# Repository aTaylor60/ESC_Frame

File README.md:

# ESC_Frame
A combined frame and 4in1 brushless ESC running BLHeli_s with 16mm hole spacing.

Derived from the excelent [tinyPEPPER](http://fishpepper.de/projects/tinypepper/) project by http://fishpepper.de As such I have also used the fishpepper KiCad resources - [kicad_misc](https://github.com/fishpepper/kicad_misc) 

Until I write a proper build guide the [tinyPEPPER v0.5](http://fishpepper.de/2017/03/23/tinypepper-esc-how-to-build-your-own-v0-5/) build guide will be the best reference.

Key features:
- Frame integrated ESC reduces stack height
- 83mm motor-to-motor frame size suits BR1103b motors
- 16x16mm hole-to-hole spacing for FC
- BLHeli_S with DSHOT300
- 1S only

This work is published under the CERN open hardware license v1.2. 
Feel free to use the design - but make sure to give proper credit 
and release all modifications under the same license! 

This comes with NO warranty, build and fly at your own risk!

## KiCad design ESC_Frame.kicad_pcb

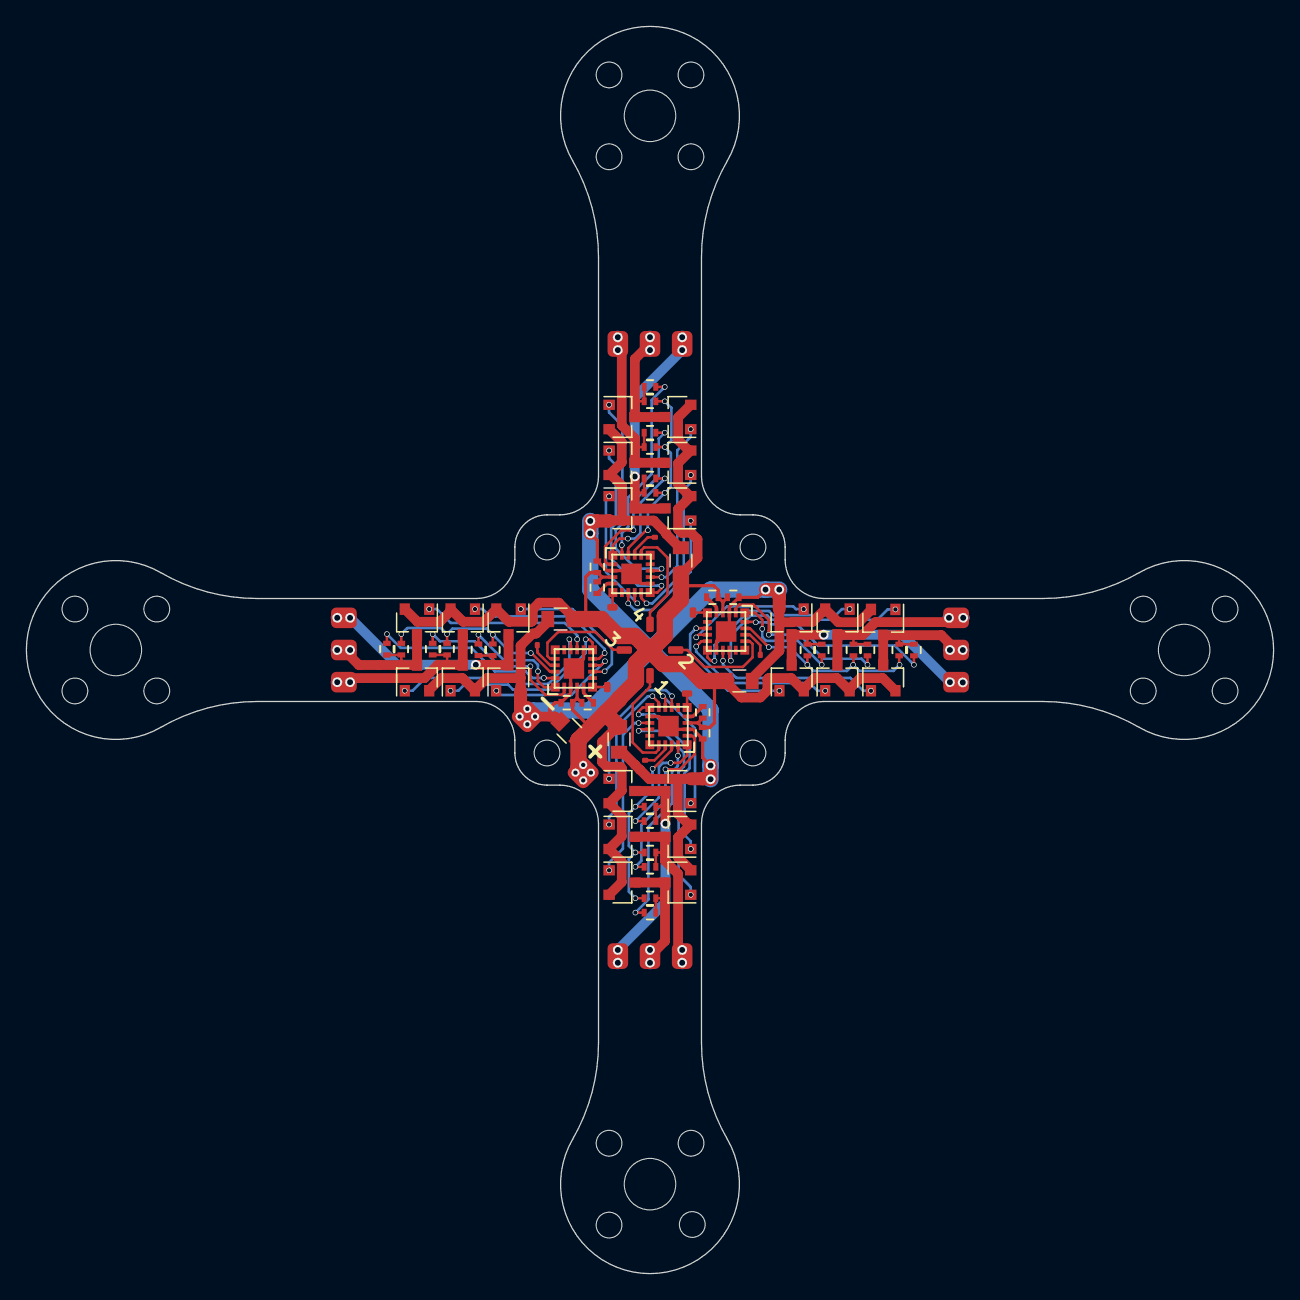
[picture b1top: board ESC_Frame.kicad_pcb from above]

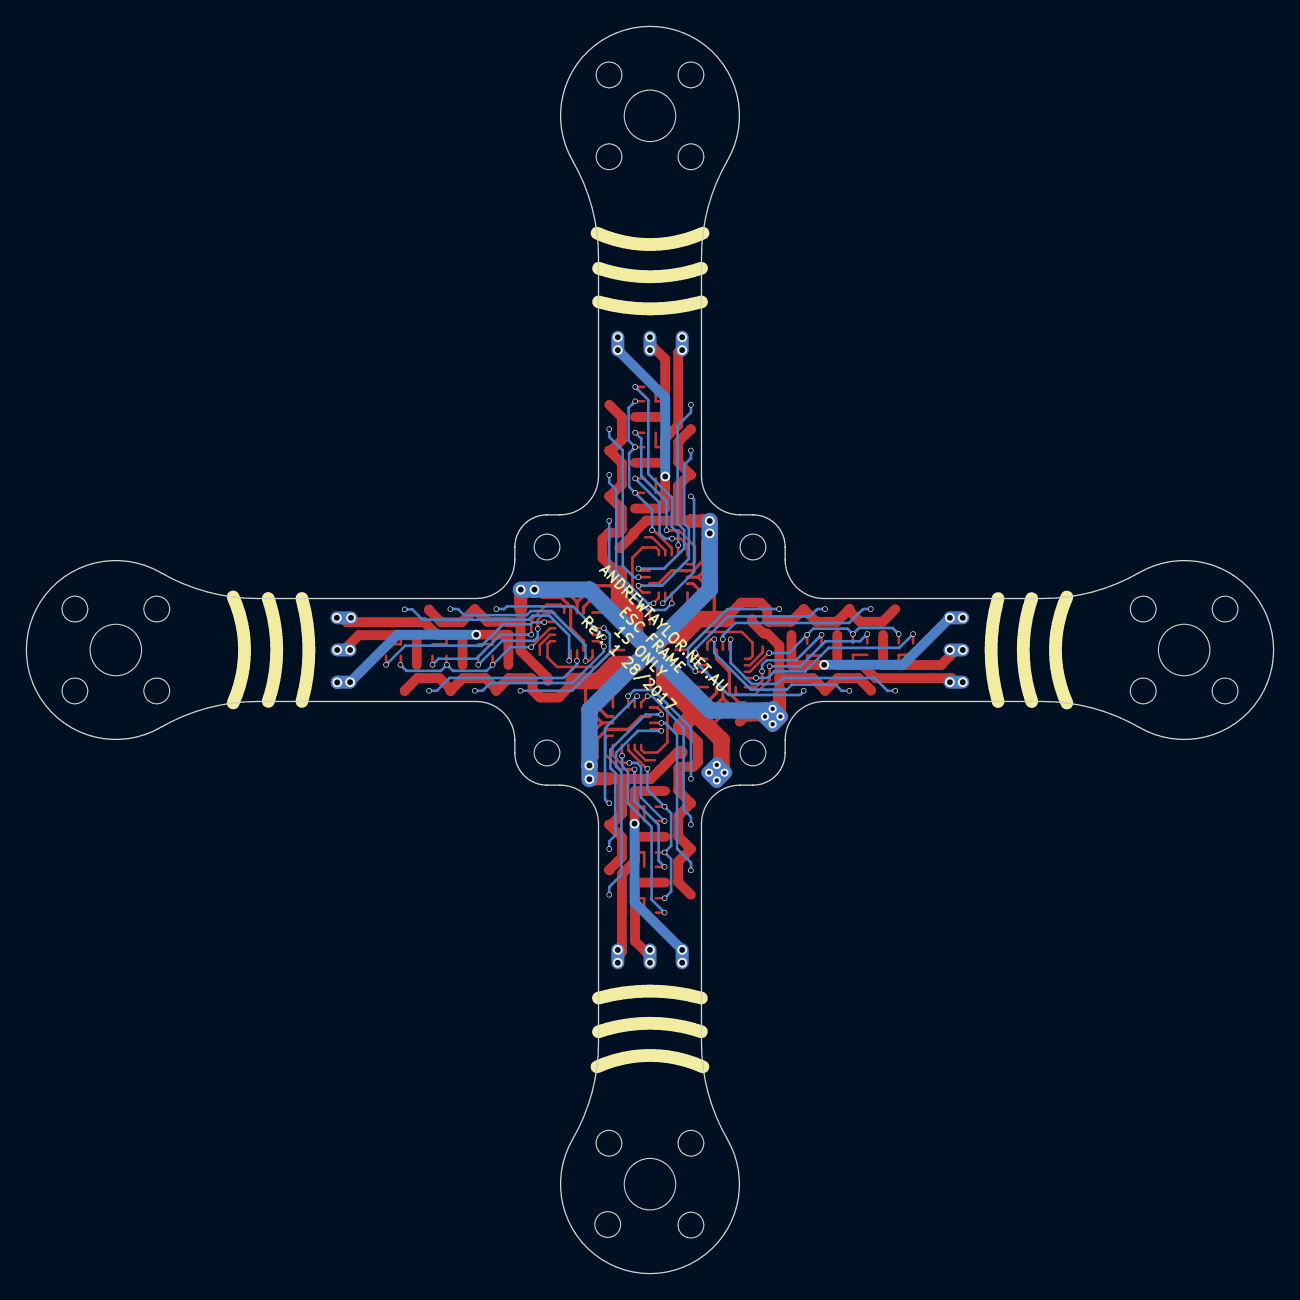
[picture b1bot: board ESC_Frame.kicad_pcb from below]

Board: 2 copper layers, 96.9 x 96.9 mm, 117 parts (2 on the bottom side), 70 nets.

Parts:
BL_TX1, BL_TX2, BL_TX3, BL_TX4: TP; TP_smd_0.5x0.4
C201, C301, C401, C501, C1000: 47u; C_0805
C202, C302, C402, C502: 100n; C_0402_CUSTOM
FET201, FET203, FET205, FET301, FET303, FET305, FET401, FET403, FET405, FET501, FET503, FET505: IRLML6244; SOT-23
FET202, FET204, FET206, FET302, FET304, FET306, FET402, FET404, FET406, FET502, FET504, FET506: IRLML2244; SOT-23
H1, H2, H3, H4, H5, H6, H7, H8, H9, H10, H11, H12, H13, H14, H15, H16, H17, H18, H19, H20: hole; mouting_hole
H21, H22, H23, H24: hole; MountingHole_4mm
Out_A1, Out_A2, Out_A3, Out_A4: TP; SolderWirePad_single_1-2mmDrill
Out_B1, Out_B2, Out_B3, Out_B4: TP; SolderWirePad_single_1-2mmDrill
Out_C1, Out_C2, Out_C3, Out_C4: TP; SolderWirePad_single_1-5mmDrill
R201, R202, R204, R206, R301, R302, R304, R306, R401, R402, R404, R406, R501, R502, R504, R506: 1k; R_0402_CUSTOM
R203, R205, R207, R303, R305, R307, R403, R405, R407, R503, R505, R507: 10k; R_0402_CUSTOM
TP1, TP2, TP101, TP102: TP; TP_powerpad
TP103, TP104, TP105, TP106: TP; tp_SMD_0.6x1.2
TP202, TP302, TP402, TP502: TP; TP_smd_0.5x0.8
U201, U301, U401, U501: EFM8BB21; QFN20

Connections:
/RC_IN_0: TP103.1, U201.17
/RC_IN_1: TP104.1, U301.17
/single esc 1/Ac_0: FET202.1, U201.13
/single esc 1/Ap_0: FET201.1, U201.14
/single esc 1/Bc_0: FET204.1, U201.10
/single esc 1/Bp_0: FET203.1, U201.11
/single esc 1/C2D_0: TP202.1, U201.6
/single esc 1/Cc_0: FET206.1, U201.8
/single esc 1/Cp_0: FET205.1, U201.9
/single esc 1/PHASE_A_0: FET201.3, FET202.3, Out_A1.1, R202.2, R203.1
/single esc 1/PHASE_B_0: FET203.3, FET204.3, Out_B1.1, R204.2, R205.1
/single esc 1/PHASE_C_0: FET205.3, FET206.3, Out_C1.1, R206.1, R207.1
/single esc 2/Ac_0: FET302.1, U301.13
/single esc 2/Ap_0: FET301.1, U301.14
/single esc 2/Bc_0: FET304.1, U301.10
/single esc 2/Bp_0: FET303.1, U301.11
/single esc 2/C2D_0: TP302.1, U301.6
/single esc 2/Cc_0: FET306.1, U301.8
/single esc 2/Cp_0: FET305.1, U301.9
/single esc 2/PHASE_A_0: FET301.3, FET302.3, Out_A2.1, R302.2, R303.1
/single esc 2/PHASE_B_0: FET303.3, FET304.3, Out_B2.1, R304.2, R305.1
/single esc 2/PHASE_C_0: FET305.3, FET306.3, Out_C2.1, R306.1, R307.1
/single esc 3/Ac_0: FET402.1, U401.13
/single esc 3/Ap_0: FET401.1, U401.14
/single esc 3/Bc_0: FET404.1, U401.10
/single esc 3/Bp_0: FET403.1, U401.11
/single esc 3/C2D_0: TP402.1, U401.6
/single esc 3/Cc_0: FET406.1, U401.8
/single esc 3/Cp_0: FET405.1, U401.9
/single esc 3/PHASE_A_0: FET401.3, FET402.3, Out_A3.1, R402.2, R403.1
/single esc 3/PHASE_B_0: FET403.3, FET404.3, Out_B3.1, R404.2, R405.1
/single esc 3/PHASE_C_0: FET405.3, FET406.3, Out_C3.1, R406.1, R407.1
/single esc 3/RC_IN: TP105.1, U401.17
/single esc 4/Ac_0: FET502.1, U501.13
/single esc 4/Ap_0: FET501.1, U501.14
/single esc 4/Bc_0: FET504.1, U501.10
/single esc 4/Bp_0: FET503.1, U501.11
/single esc 4/C2D_0: TP502.1, U501.6
/single esc 4/Cc_0: FET506.1, U501.8
/single esc 4/Cp_0: FET505.1, U501.9
/single esc 4/PHASE_A_0: FET501.3, FET502.3, Out_A4.1, R502.2, R503.1
/single esc 4/PHASE_B_0: FET503.3, FET504.3, Out_B4.1, R504.2, R505.1
/single esc 4/PHASE_C_0: FET505.3, FET506.3, Out_C4.1, R506.1, R507.1
/single esc 4/RC_IN: TP106.1, U501.17
GND: C201.1, C202.1, C301.1, C302.1, C401.1, C402.1, C501.1, C502.1, C1000.1, FET201.2, FET203.2, FET205.2, FET301.2, FET303.2, FET305.2, FET401.2, FET403.2, FET405.2, FET501.2, FET503.2, FET505.2, TP2.1, TP102.1, U201.3, U201.12, U201.21, U301.3, U301.12, U301.21, U401.3, U401.12, U401.21, U501.3, U501.12, U501.21
unnamed: BL_TX1.1, U201.18
unnamed: BL_TX2.1, U301.18
unnamed: BL_TX3.1, U401.18
unnamed: BL_TX4.1, U501.18
unnamed: R201.1, U201.5
unnamed: R202.1, R204.1, R206.2, U201.19
unnamed: R203.2, U201.20
unnamed: R205.2, U201.2
unnamed: R207.2, U201.1
unnamed: R301.1, U301.5
unnamed: R302.1, R304.1, R306.2, U301.19
unnamed: R303.2, U301.20
unnamed: R305.2, U301.2
unnamed: R307.2, U301.1
unnamed: R401.1, U401.5
unnamed: R402.1, R404.1, R406.2, U401.19
unnamed: R403.2, U401.20
unnamed: R405.2, U401.2
unnamed: R407.2, U401.1
unnamed: R501.1, U501.5
unnamed: R502.1, R504.1, R506.2, U501.19
unnamed: R503.2, U501.20
unnamed: R505.2, U501.2
unnamed: R507.2, U501.1
VCC: C201.2, C202.2, C301.2, C302.2, C401.2, C402.2, C501.2, C502.2, C1000.2, FET202.2, FET204.2, FET206.2, FET302.2, FET304.2, FET306.2, FET402.2, FET404.2, FET406.2, FET502.2, FET504.2, FET506.2, R201.2, R301.2, R401.2, R501.2, TP1.1, TP101.1, U201.4, U301.4, U401.4, U501.4

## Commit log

2017-11-08 Added image
